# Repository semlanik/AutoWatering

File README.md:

**Parts are used in the project**
- [Moisture sensors](https://www.amazon.de/gp/product/B088LPJL7Q/ref=ppx_yo_dt_b_asin_title_o04_s01?ie=UTF8&psc=1)
- [Pumps](https://www.amazon.de/-/en/gp/product/B07J5CY7B8/ref=ppx_yo_dt_b_asin_title_o08_s01?ie=UTF8&psc=1)
- [Junctions](https://www.amazon.de/gp/product/B09C8CJPG7/ref=ppx_yo_dt_b_asin_title_o03_s00?ie=UTF8&psc=1)
- [LDO](https://www.reichelt.de/ldo-spannungsregler-fix-5-v-800ma-sot-223-lm-1117-mp5-0-p109330.html?&nbc=1)
- [N-Channel FETs](https://www.reichelt.de/mosfet-n-kanal-20-v-4-2-a-rds-on-0-045-ohm-sot-23-irlml-2502-p108737.html?&nbc=1)
- [Arduino](https://www.reichelt.de/arduino-nano-every-atmega4809-mit-header-ard-nano-eve-h-p261301.html?&nbc=1)
- Misc: resistors, capacitors

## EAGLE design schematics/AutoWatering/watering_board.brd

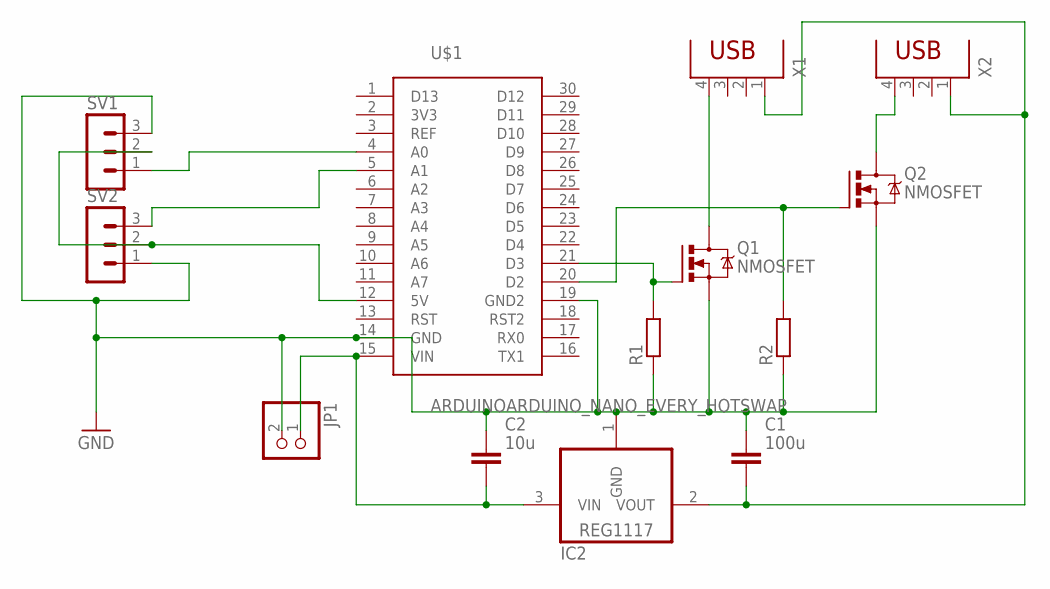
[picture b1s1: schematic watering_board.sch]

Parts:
C1: 100u; CAPC3216X135
C2: 10u; CAPC3216X135
IC2: REG1117; SOT223
JP1: PINHD-1X2; 1X02
Q1, Q2: NMOSFET; SOT23
R1, R2: R-EU_M1206; M1206
SV1, SV2: MA03-1
U$1: ARDUINOARDUINO_NANO_EVERY_HOTSWAP; DIP1524W80P254L4318H508Q30B
X1, X2: PN87520

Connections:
3V3: U$1.2 (3V3)
GND: C1.1, C2.1, IC2.1 (GND), JP1.2, Q1.2 (S), Q2.2 (S), R1.1, R2.1, SV1.3, SV2.1, U$1.14 (GND), U$1.19 (GND2)
unnamed: SV1.1, U$1.4 (A0)
unnamed: SV2.3, U$1.5 (A1)
unnamed: SV1.2, SV2.2, U$1.12 (5V)
unnamed: C2.2, IC2.3 (VIN), JP1.1, U$1.15 (VIN)
unnamed: Q2.1 (G), R2.2, U$1.20 (D2)
unnamed: Q1.3 (D), X1.4
unnamed: Q2.3 (D), X2.4
unnamed: Q1.1 (G), R1.2, U$1.21 (D3)
unnamed: C1.2, IC2.2 (VOUT), X1.1, X2.1

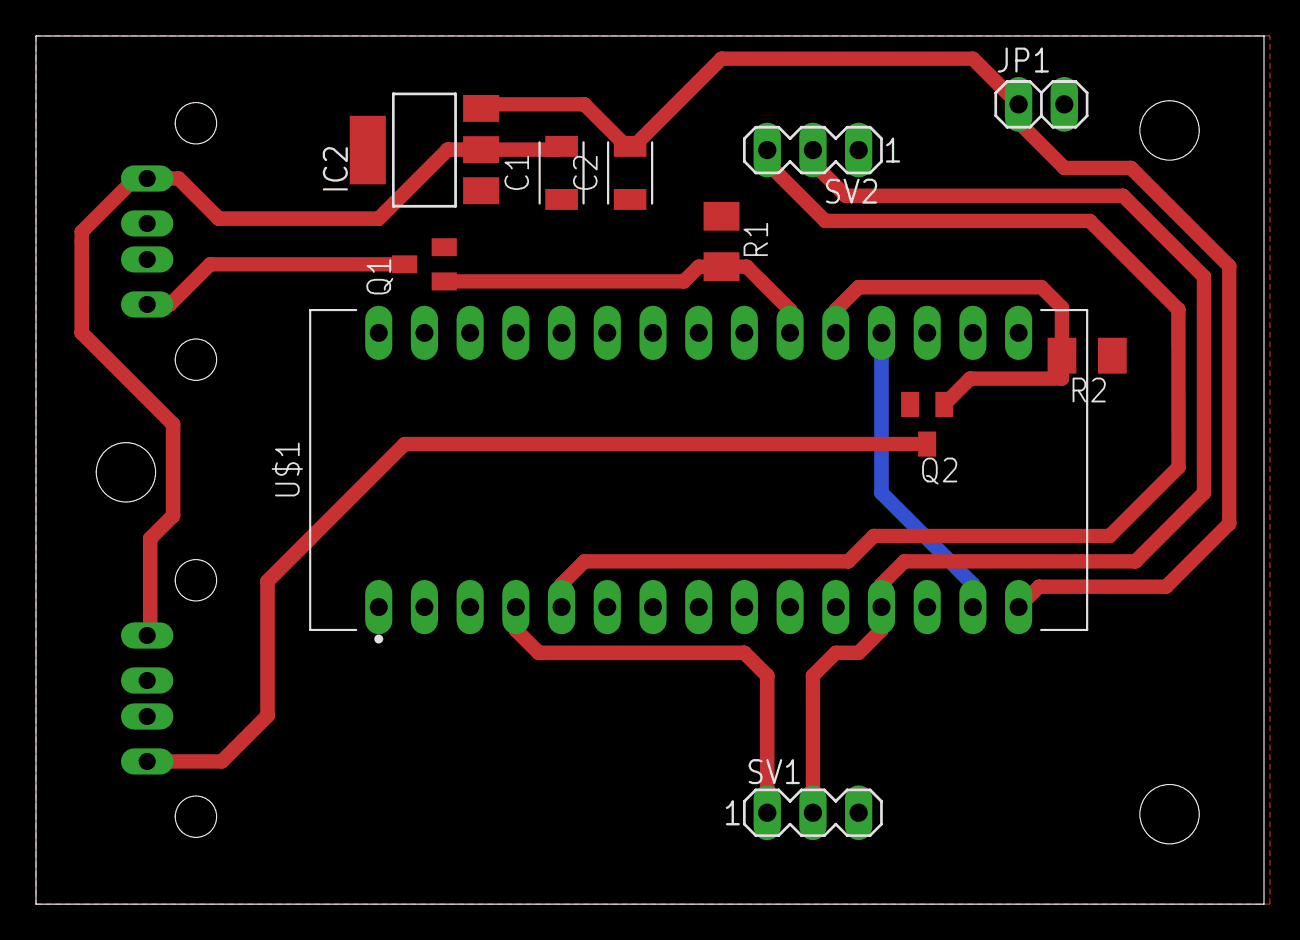
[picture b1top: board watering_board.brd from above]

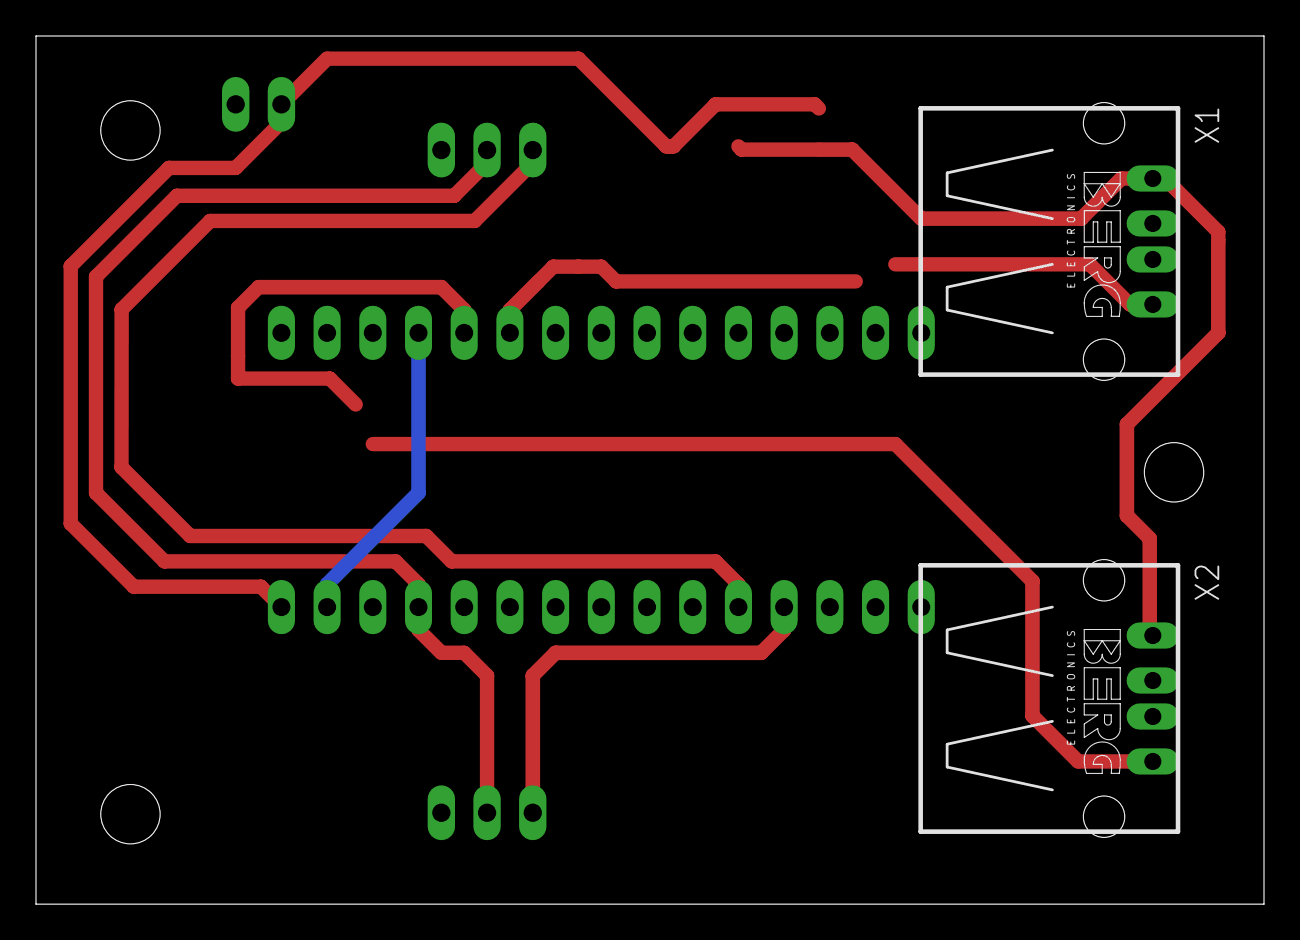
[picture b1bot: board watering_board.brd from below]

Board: 2 copper layers, 68.2 x 48.2 mm, 13 parts (2 on the bottom side), 10 nets.

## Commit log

2022-04-08 Add missing LSO capacitors
2022-04-10 Recalibrate sensors
2022-04-15 Add powersafe mode
    Add powersafe mode for arduino with watch dog wake up mechanism.
    Add nozzle 3d model and grbl file.
2022-04-15 Add readme
2022-05-02 Add an extra deplay after sleep before reading sensors
2022-05-26 Use USB A conntector for the pump
2022-05-26 Update the pump model
2022-05-29 Add the case
    Add the case for the schematics.
    Update to Arduino every. Use the difference sleep/wakeup mechnism.
    Adjust moisture sensors.
    Update schematics to match the case.
